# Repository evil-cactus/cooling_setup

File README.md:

# cooling_setup

streamlit dependencies:
	'python'
	'python-altair>=3.2.0'
	'python-astor'
	'python-base58'
	'python-blinker'
	'python-cachetools>=4.0'
	'python-click>=7.0'
	'python-numpy'
	'python-packaging'
	'python-pandas>=0.21.0'
	'python-pillow>=6.2.0'
	'python-protobuf>=3.11.2'
	'python-pyarrow'
	'python-dateutil'
	'python-requests'
	'python-toml'
	'python-tornado'
	'python-tzlocal'
	'python-validators'
	'python-watchdog'
	'python-gitpython'
  
 pip install streamlit
 pip install pydeck
 
 please add other dependencies when you encounter them!

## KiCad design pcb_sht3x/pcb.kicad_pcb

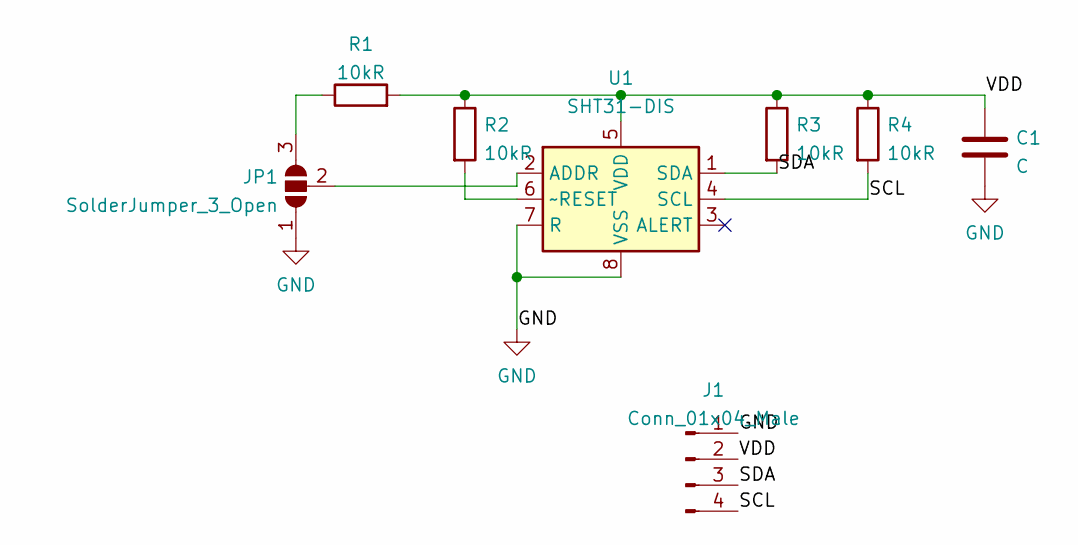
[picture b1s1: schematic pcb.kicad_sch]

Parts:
C1: C; C_0603_1608Metric_Pad1.08x0.95mm_HandSolder
J1: Conn_01x04_Male; PinHeader_1x04_P2.00mm_Vertical
JP1: SolderJumper_3_Open; SolderJumper-3_P1.3mm_Open_RoundedPad1.0x1.5mm
R1, R2, R3, R4: 10kR; R_0603_1608Metric_Pad0.98x0.95mm_HandSolder
U1: SHT31-DIS; Sensirion_DFN-8-1EP_2.5x2.5mm_P0.5mm_EP1.1x1.7mm_wider_pads

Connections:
/SCL: J1.4, R4.2, U1.4 (SCL)
/SDA: J1.3, R3.2, U1.1 (SDA)
/VDD: C1.1, J1.2, R1.2, R2.1, R3.1, R4.1, U1.5 (VDD)
GND: C1.2, J1.1, JP1.1 (A), U1.7 (R), U1.8 (VSS), U1.9 (VSS)
unnamed: JP1.2 (C), U1.2 (ADDR)
unnamed: JP1.3 (B), R1.1
unnamed: R2.2, U1.6 (~RESET)

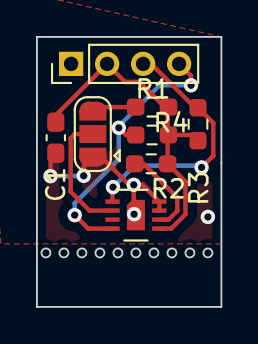
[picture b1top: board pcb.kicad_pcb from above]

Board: 2 copper layers, 10.2 x 15.0 mm, 8 parts (0 on the bottom side), 7 nets.

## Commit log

2021-11-15 monitoring code
2021-11-15 test
2021-11-18 update_18/11/21
2021-11-25 update 25/11/21
2021-11-30 update 30/11/21
2021-12-01 added doc for ps
2021-12-01 test github
2021-12-01 test 2 github
2021-12-13 update 13/12/21
2021-12-15 update 15/12/21
    - changed Arduino-file structure
    - small changes to py-files
2022-01-20 Changes on input procedure; not finished yet
2022-01-26 new input method; full automation possible now
2022-01-31 Update for RasPi
2022-01-31 removed some junk
2022-01-31 RasPi updata2
2022-02-02 measurements update
2022-02-03 Measurements
2022-02-04 Measurements new peltier
2022-02-07 Measurements Peltier 2 Nr.2
2022-02-07 analysis_update
2022-03-08 update files
2022-05-13 i2c scanner
2022-05-13 new input and monitoring version
2022-06-06 used version to collect data at desy
